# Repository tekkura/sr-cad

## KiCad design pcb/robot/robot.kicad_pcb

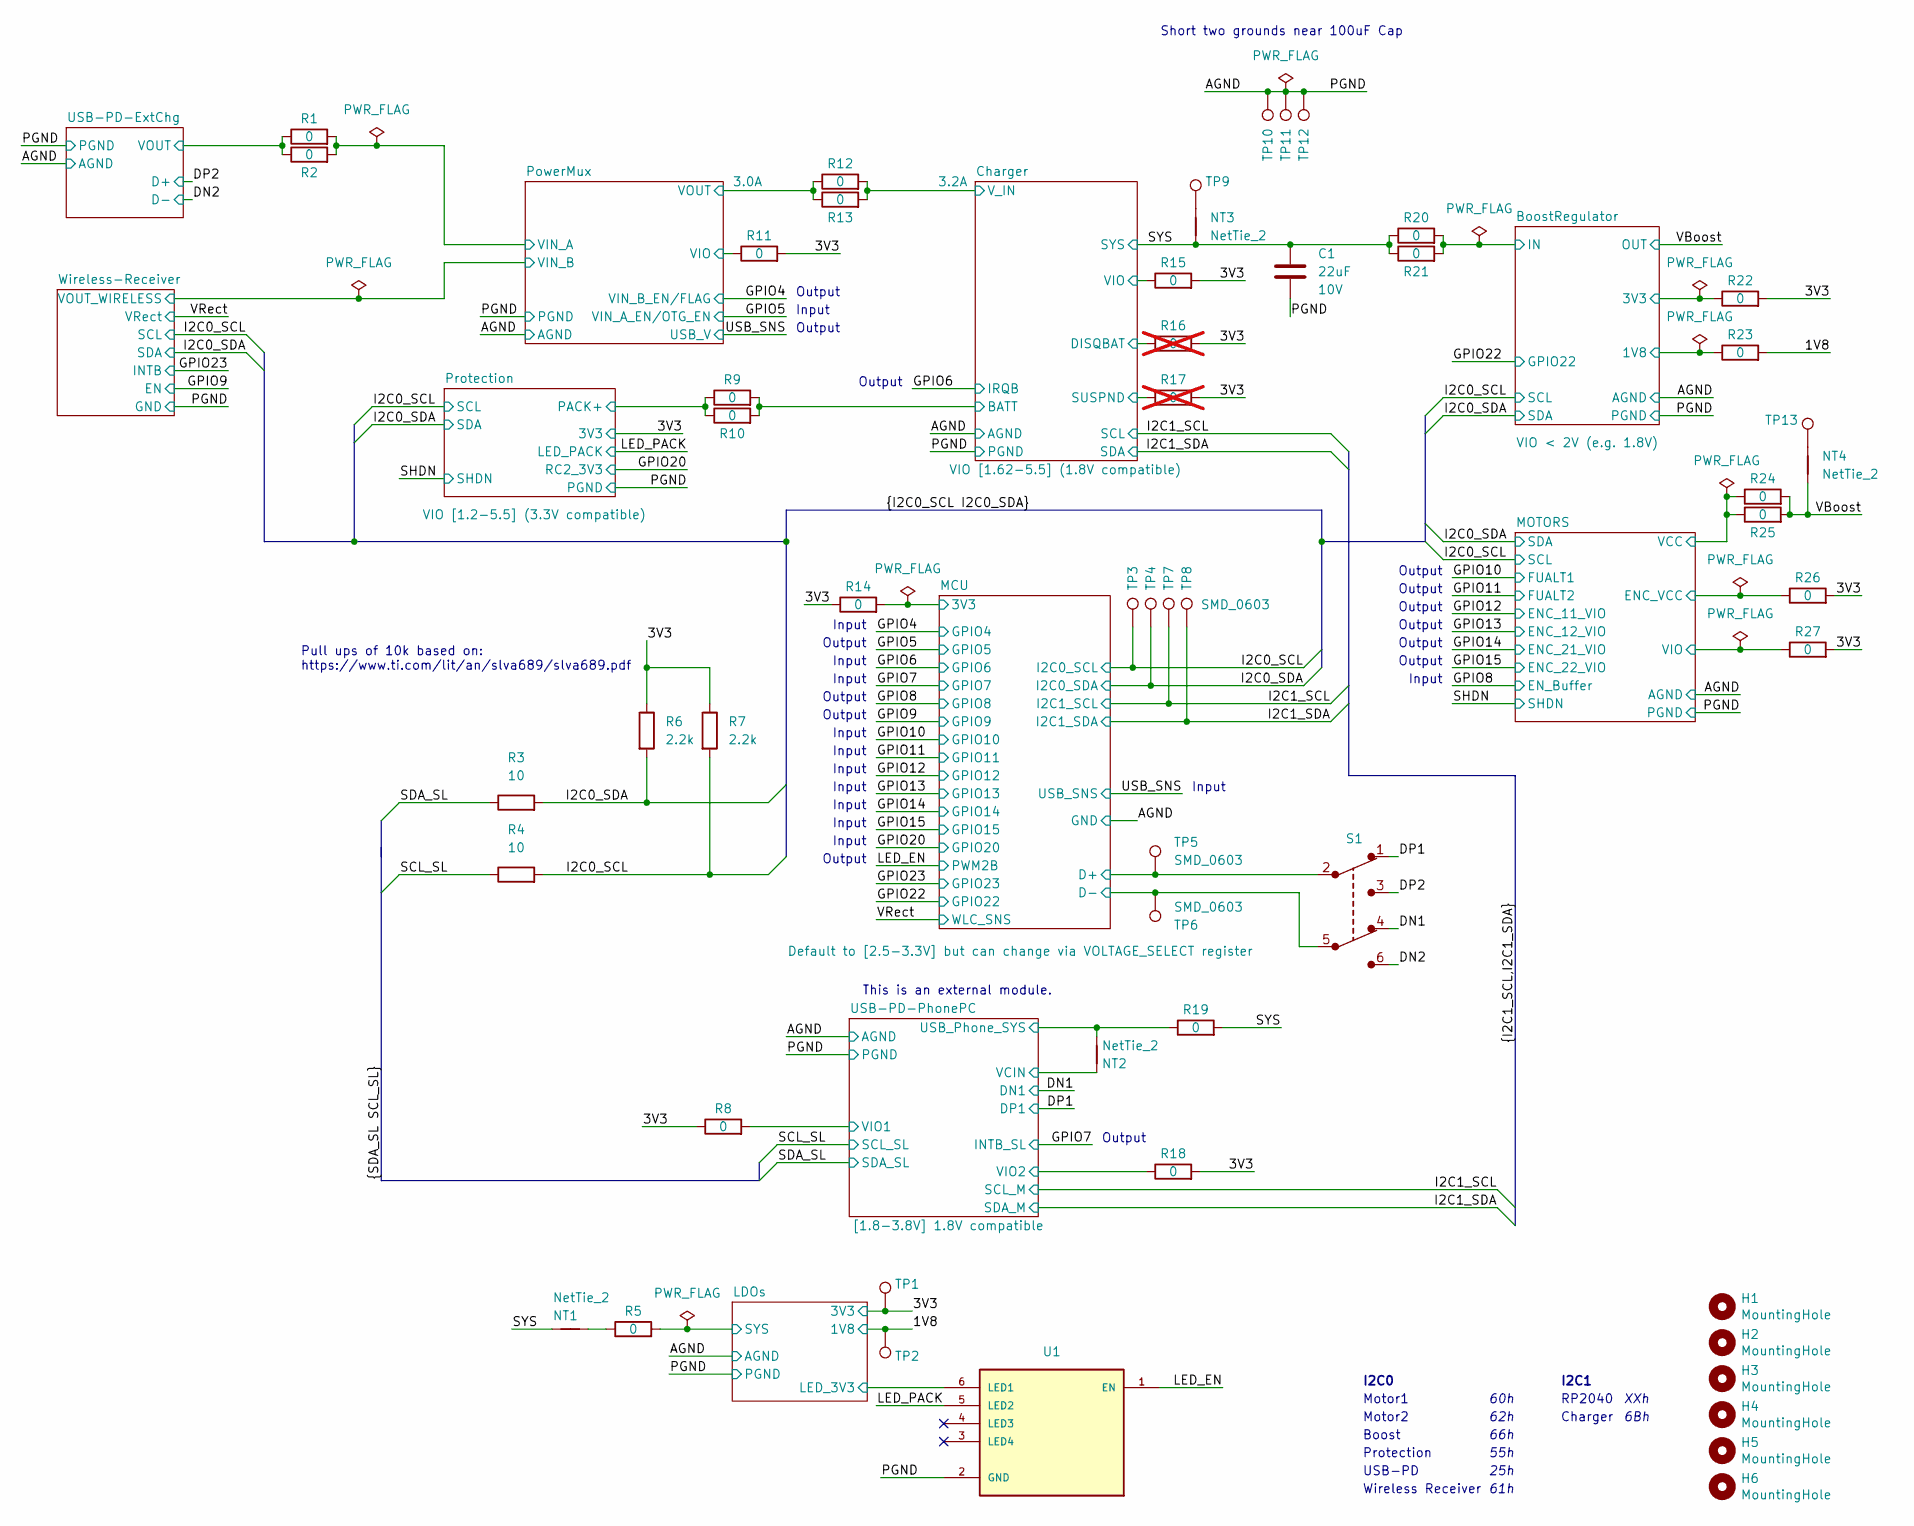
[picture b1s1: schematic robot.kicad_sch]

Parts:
C1: 22uF; C_0603_1608Metric; Part Number GRM188R61A226ME15D
H1, H2, H5, H6: MountingHole; MountingHole_2.2mm_M2_2mm_clearance; Part Number N/A
H3, H4: MountingHole; MountingHole_2.2mm_M2; Part Number N/A
NT1, NT2, NT3, NT4: NetTie_2; NetTie-_SMD_Pad6mil; Part Number N/A
R1, R2, R9, R10, R12, R13, R19, R20, R21, R24, R25: 0; R_0805_2012Metric; Part Number RMCF0805ZT0R00
R3, R4: 10; R_0402_1005Metric; Part Number RC0402FR-1310RL
R5, R8, R11, R14, R15, R18, R22, R23, R26, R27: 0; R_0603_1608Metric; Part Number RMCF0603ZT0R00
R6, R7: 2.2k; R_0603_1608Metric; Part Number RMCF0603JT2K20
R16, R17: 0; R_0603_1608Metric; Part Number RMCF0603ZT0R00; not fitted
S1: JS202011JCQN; SW_JS202011JCQN; Part Number JS202011JCQN
TP1, TP2, TP9, TP10, TP11, TP12, TP13: TestPoint; KEYSTONE_5002; Part Number 5002
TP3, TP4, TP5, TP6, TP7, TP8: SMD_0603; TestPoint_SMD_0603; Part Number RCUCTE
U1: AP2502KTR-G1; SOT95P280X145-6N; Part Number AP2502KTR-G1

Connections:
/1V8: R23.2, TP2.1; also elsewhere on the board
/3V3: R6.1, R7.1, R8.1, R11.2, R14.1, R15.2, R16.2, R17.2, R18.2, R22.2, R26.2, R27.2, TP1.1; also elsewhere on the board
/BoostRegulator/1V8: R23.1; also elsewhere on the board
/BoostRegulator/3V3: R22.1; also elsewhere on the board
/BoostRegulator/IN: R20.2, R21.2; also elsewhere on the board
/Charger/BATT: R9.2, R10.2; also elsewhere on the board
/Charger/DISQBAT: R16.1; also elsewhere on the board
/Charger/SUSPND: R17.1; also elsewhere on the board
/Charger/VIO: R15.1; also elsewhere on the board
/Charger/V_IN: R12.2, R13.2; also elsewhere on the board
/DN1: S1.4; also elsewhere on the board
/DN2: S1.6; also elsewhere on the board
/DP1: S1.1; also elsewhere on the board
/DP2: S1.3; also elsewhere on the board
/I2C0_SCL: R4.2, R7.2, TP3.1; also elsewhere on the board
/I2C0_SDA: R3.2, R6.2, TP4.1; also elsewhere on the board
/I2C1_SCL: TP7.1; also elsewhere on the board
/I2C1_SDA: TP8.1; also elsewhere on the board
/LDOs/LED_3V3: U1.6 (LED1); also elsewhere on the board
/LDOs/SYS: R5.2; also elsewhere on the board
/LED_EN: U1.1 (EN); also elsewhere on the board
/LED_PACK: U1.5 (LED2); also elsewhere on the board
/MCU/3V3: R14.2; also elsewhere on the board
/MCU/D+: S1.2, TP5.1; also elsewhere on the board
/MCU/D-: S1.5, TP6.1; also elsewhere on the board
/MOTORS/ENC_VCC: R26.1; also elsewhere on the board
/MOTORS/VCC: R24.1, R25.1; also elsewhere on the board
/MOTORS/VIO: R27.1; also elsewhere on the board
/PowerMux/VIN_A: R1.2, R2.2; also elsewhere on the board
/PowerMux/VIO: R11.1; also elsewhere on the board
/PowerMux/VOUT: R12.1, R13.1; also elsewhere on the board
/Protection/PACK+: R9.1, R10.1; also elsewhere on the board
/SCL_SL: R4.1; also elsewhere on the board
/SDA_SL: R3.1; also elsewhere on the board
/SYS: C1.1, NT1.1, NT3.2, R19.2, R20.1, R21.1; also elsewhere on the board
/USB-PD-ExtChg/VOUT: R1.1, R2.1; also elsewhere on the board
/USB-PD-PhonePC/USB_Phone_SYS: NT2.2, R19.1; also elsewhere on the board
/USB-PD-PhonePC/VCIN: NT2.1; also elsewhere on the board
/USB-PD-PhonePC/VIO1: R8.2; also elsewhere on the board
/USB-PD-PhonePC/VIO2: R18.1; also elsewhere on the board
/VBoost: NT4.2, R24.2, R25.2; also elsewhere on the board
GND: C1.2, TP10.1, TP11.1, TP12.1, U1.2 (GND); also elsewhere on the board
unnamed: NT1.2, R5.1
unnamed: NT3.1, TP9.1
unnamed: NT4.1, TP13.1

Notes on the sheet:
55h
Input
66h
Output
Protection
XXh
61h
Boost
I2C1
Wireless Receiver
Motor1
62h
Motor2
25h
Charger
This is an external module.
Pull ups of 10k based on: https://www.ti.com/lit/an/slva689/slva689.pdf
I2C0
USB-PD
RP2040
60h
6Bh
Short two grounds near 100uF Cap

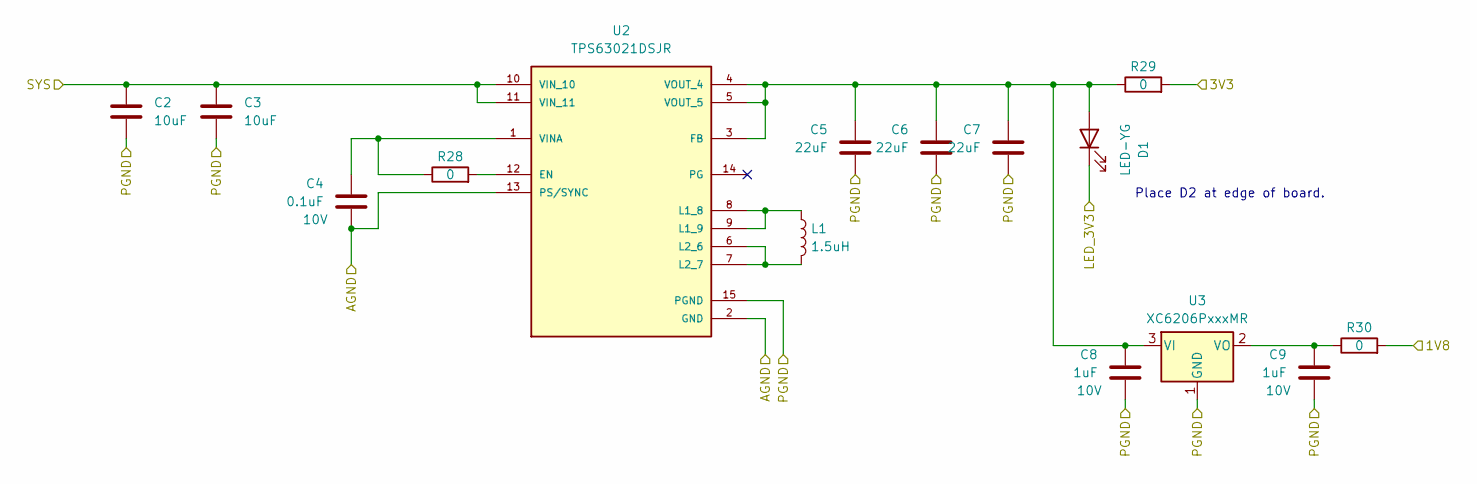
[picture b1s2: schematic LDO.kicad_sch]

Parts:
C2, C3: 10uF; C_0603_1608Metric; Part Number GRM188R61E106KA73J
C4: 0.1uF; C_0402_1005Metric; Part Number CL05A104KA5NNNC
C5, C6, C7: 22uF; C_0603_1608Metric; Part Number GRM188R61A226ME15D
C8, C9: 1uF; C_0402_1005Metric; Part Number GRM155R61E105KA12D
D1: LED-YG; B12H1UYG-20D000134U1930; Part Number B12H1UYG-20D000134U1930
L1: 1.5uH; NRS6028T1R5NMGJ; Part Number NRS6028T1R5NMGJ
R28, R29, R30: 0; R_0603_1608Metric; Part Number RMCF0603ZT0R00
U2: TPS63021DSJR; IC_TPS63021DSJR; PARTREV I; DigiKey_Part_Number 296-27259-1-ND
U3: XC6206PxxxMR; SOT-23-3; Part Number C49195704

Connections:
/1V8: R30.2; also elsewhere on the board
/3V3: R29.2; also elsewhere on the board
/LDOs/LED_3V3: D1.1 (K); also elsewhere on the board
/LDOs/SYS: C2.2, C3.2, U2.10 (VIN_10), U2.11 (VIN_11); also elsewhere on the board
GND: C2.1, C3.1, C4.2, C5.2, C6.2, C7.2, C8.2, C9.2, U2.2 (GND), U2.13 (PS/SYNC), U2.15 (PGND), U3.1 (GND); also elsewhere on the board
unnamed: C5.1, C6.1, C7.1, C8.1, D1.2 (A), R29.1, U2.3 (FB), U2.4 (VOUT_4), U2.5 (VOUT_5), U3.3 (VI)
unnamed: R28.2, U2.12 (EN)
unnamed: L1.1, U2.8 (L1_8), U2.9 (L1_9)
unnamed: L1.2, U2.6 (L2_6), U2.7 (L2_7)
unnamed: C4.1, R28.1, U2.1 (VINA)
unnamed: C9.1, R30.1, U3.2 (VO)

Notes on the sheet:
Place D2 at edge of board.

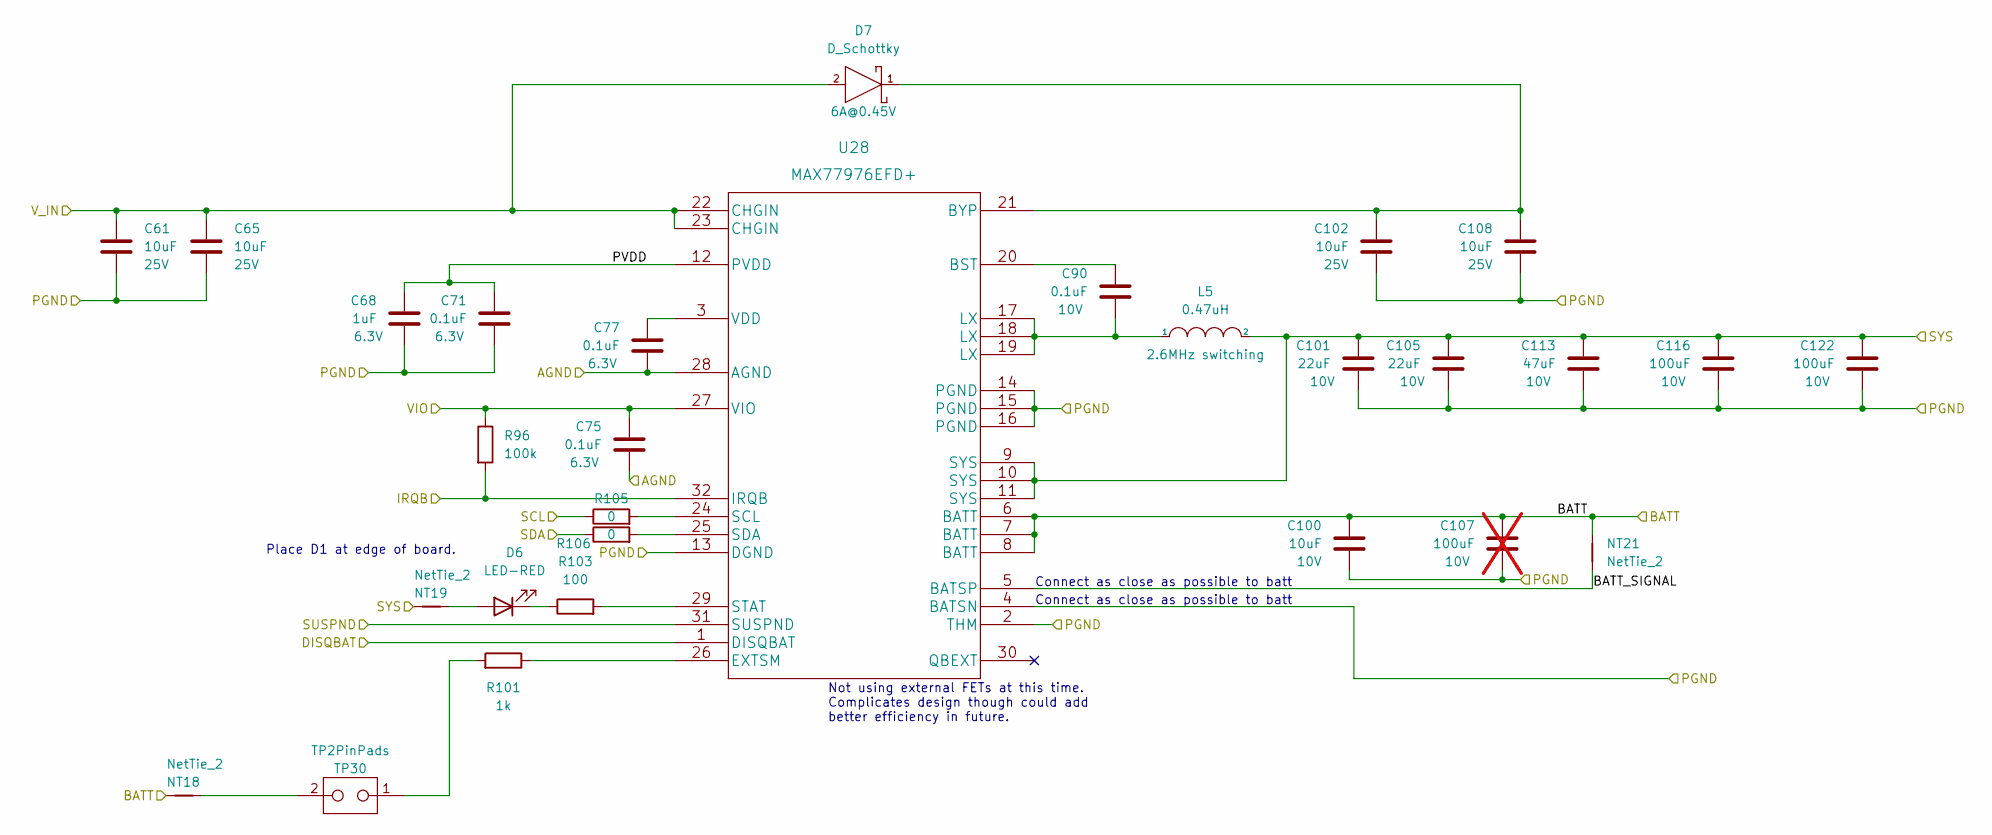
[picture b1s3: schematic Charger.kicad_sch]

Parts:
C61, C65, C100, C102, C108: 10uF; C_0603_1608Metric; Part Number GRM188R61E106KA73J
C68: 1uF; C_0402_1005Metric; Part Number GRM155R61E105KA12D
C71, C75, C77, C90: 0.1uF; C_0402_1005Metric; Part Number CL05A104KA5NNNC
C101, C105: 22uF; C_0603_1608Metric; Part Number GRM188R61A226ME15D
C107: 100uF; C_1206_3216Metric; Part Number GRM31CD80J107MEA8K; not fitted
C113: 47uF; C_0805_2012Metric; Part Number CL21A476MRYNNNE
C116, C122: 100uF; C_1206_3216Metric; Part Number GRM31CD80J107MEA8K
D6: LED-RED; B12H1UYG-20D000134U1930; Part Number B12H1USD-20D000234U1930
D7: D_Schottky; SD2114S040S8R0; Part Number SD2114S040S8R0
L5: 0.47uH; Vishay-IHLP-2020BZ-FP_1.905x2.79-3D_2.0-0-0-MFG; Part Number IHLP2020BZERR47M01
NT18, NT19, NT21: NetTie_2; NetTie-_SMD_Pad6mil; Part Number N/A
R96: 100k; R_0603_1608Metric; Part Number WR06X1003FTL
R101: 1k; R_0402_1005Metric; Part Number WR04X102 JTL
R103: 100; R_0603_1608Metric; Part Number RMCF0603JT100R
R105, R106: 0; R_0603_1608Metric; Part Number RMCF0603ZT0R00
TP30: TP2PinPads; TestPoint_2Pads_Pitch2mm_SMD; Part Number N/A
U28: MAX77976EFD+; MAX77976; Part Number MAX77976EFD+

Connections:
/Charger/BATT: C100.1, C107.1, NT18.1, NT21.1, U28.6 (BATT), U28.7 (BATT), U28.8 (BATT); also elsewhere on the board
/Charger/BATT_SIGNAL: NT21.2, U28.5 (BATSP)
/Charger/DISQBAT: U28.1 (DISQBAT); also elsewhere on the board
/Charger/PVDD: C68.1, C71.1, U28.12 (PVDD)
/Charger/SUSPND: U28.31 (SUSPND); also elsewhere on the board
/Charger/VIO: C75.1, R96.1, U28.27 (VIO); also elsewhere on the board
/Charger/V_IN: C61.1, C65.1, D7.2 (Anode), U28.22 (CHGIN), U28.23 (CHGIN); also elsewhere on the board
/GPIO6: R96.2, U28.32 (IRQB); also elsewhere on the board
/I2C1_SCL: R105.1; also elsewhere on the board
/I2C1_SDA: R106.1; also elsewhere on the board
/SYS: C101.1, C105.1, C113.1, C116.1, C122.1, L5.2, NT19.1, U28.9 (SYS), U28.10 (SYS), U28.11 (SYS); also elsewhere on the board
GND: C61.2, C65.2, C68.2, C71.2, C75.2, C77.2, C100.2, C101.2, C102.2, C105.2, C107.2, C108.2, C113.2, C116.2, C122.2, U28.2 (THM), U28.4 (BATSN), U28.13 (DGND), U28.14 (PGND), U28.15 (PGND), U28.16 (PGND), U28.28 (AGND); also elsewhere on the board
unnamed: C90.2, L5.1, U28.17 (LX), U28.18 (LX), U28.19 (LX)
unnamed: D6.2 (A), NT19.2
unnamed: D6.1 (K), R103.1
unnamed: C102.1, C108.1, D7.1 (Cathode), U28.21 (BYP)
unnamed: NT18.2, TP30.2
unnamed: R101.2, TP30.1
unnamed: C90.1, U28.20 (BST)
unnamed: R101.1, U28.26 (EXTSM)
unnamed: R105.2, U28.24 (SCL)
unnamed: R106.2, U28.25 (SDA)
unnamed: R103.2, U28.29 (STAT)
unnamed: C77.1, U28.3 (VDD)

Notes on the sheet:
Not using external FETs at this time. Complicates design though could add better efficiency in future.
Connect as close as possible to batt
Place D1 at edge of board.

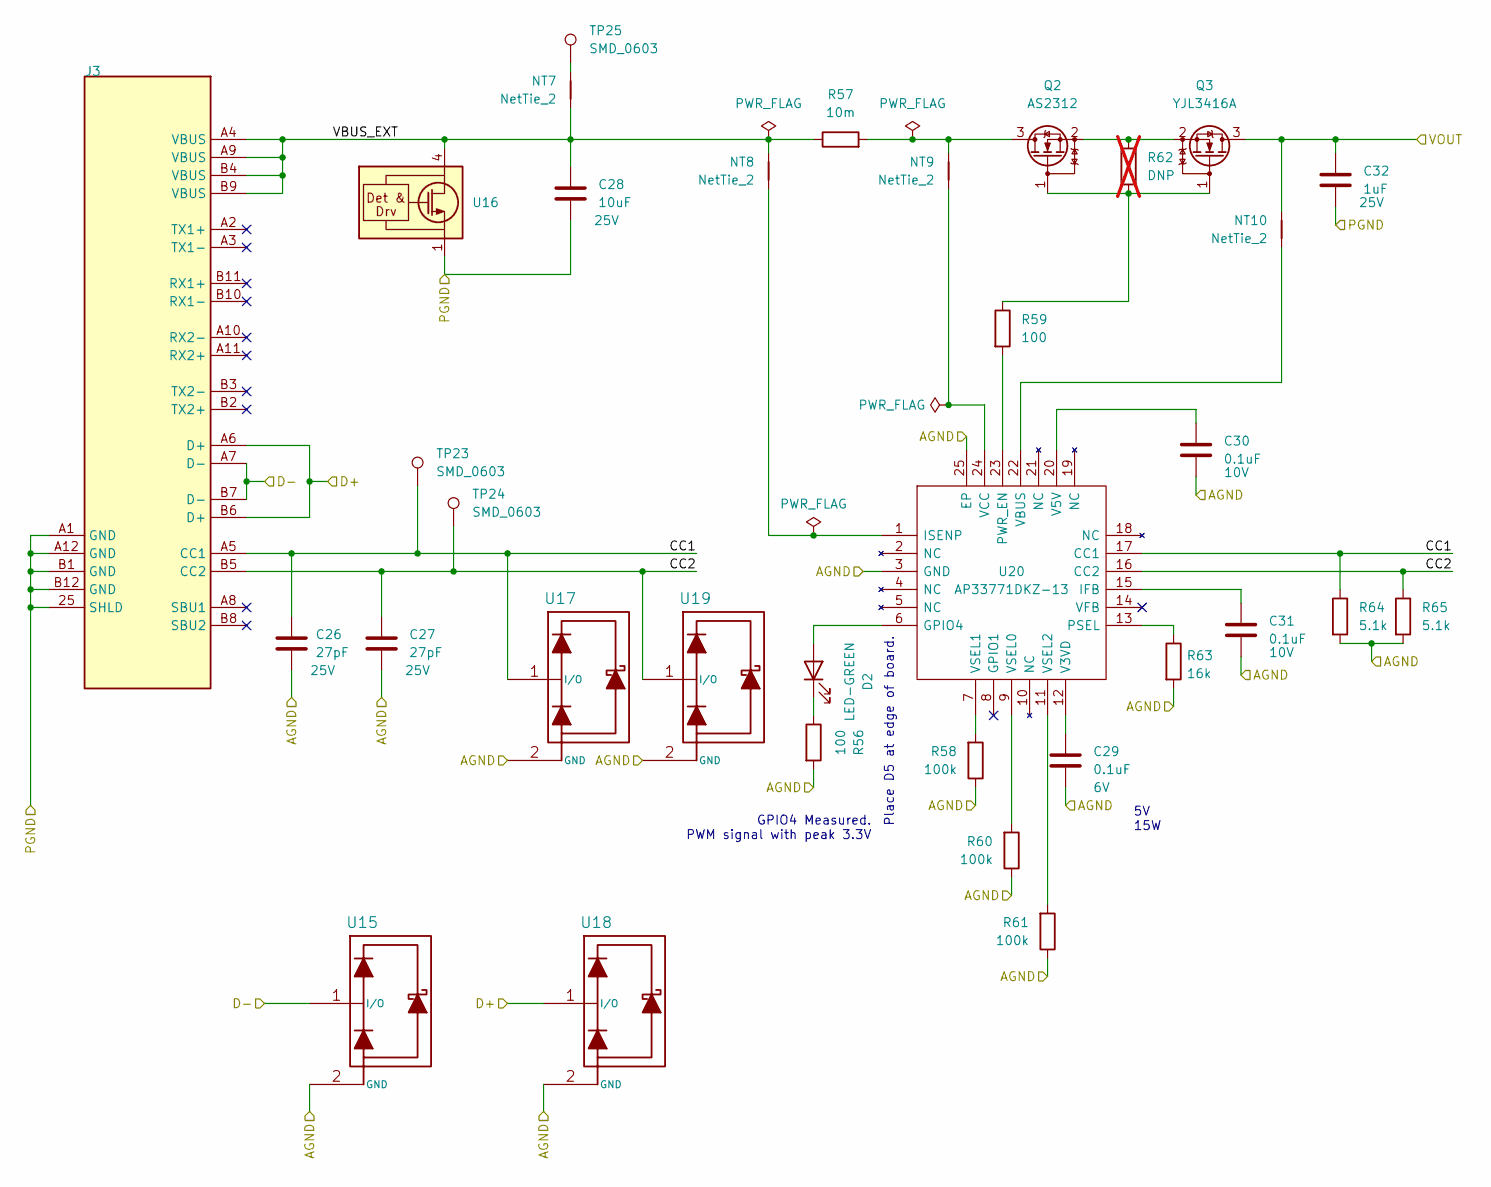
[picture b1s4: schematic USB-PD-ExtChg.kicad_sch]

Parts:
C26, C27: 27pF; C_0402_1005Metric; Part Number GRM1555C1H270JA01J
C28: 10uF; C_0603_1608Metric; Part Number GRM188R61E106KA73J
C29, C30, C31: 0.1uF; C_0402_1005Metric; Part Number CL05A104KA5NNNC
C32: 1uF; C_0402_1005Metric; Part Number GRM155R61E105KA12D
D2: LED-GREEN; B12H1UYG-20D000134U1930; Part Number B12H1NG--20D000134U1930
J3: USBC_Receptacle_SMD_RA; CON_USB3.1-C_RCPT_SMD_RA_ACP_12401610E4#2A; Part Number 12401610E4#2A
NT7, NT8, NT9, NT10: NetTie_2; NetTie-_SMD_Pad6mil; Part Number N/A
Q2: AS2312; SOT-23; Part Number AS2312
Q3: YJL3416A; SOT-23; Part Number YJL3416A
R56, R59: 100; R_0603_1608Metric; Part Number RMCF0603JT100R
R57: 10m; R_1206_3216Metric; Part Number ERJ-8CWJR010V
R58, R60, R61: 100k; R_0603_1608Metric; Part Number WR06X1003FTL
R62: DNP; R_0603_1608Metric; Part Number DNP; not fitted
R63: 16k; R_0603_1608Metric; Part Number RMCF0603FT16K0
R64, R65: 5.1k; R_0603_1608Metric; Part Number RMCF0603JT5K10
TP23, TP24, TP25: SMD_0603; TestPoint_SMD_0603; Part Number RCUCTE
U15, U17, U18, U19: TPD1E05U06; TPD1E05U06DPYR; Part Number TPD1E05U06DPYR
U16: TVS0500DRV; TVS0500DRVR; Part Number TVS0500DRVR
U20: AP33771DKZ-13; AP33771DKZ13; Part Number AP33771DKZ-13

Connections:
/DN2: J3.A7 (D-), J3.B7 (D-), U15.1 (I/O); also elsewhere on the board
/DP2: J3.A6 (D+), J3.B6 (D+), U18.1 (I/O); also elsewhere on the board
/USB-PD-ExtChg/CC1: C26.1, J3.A5 (CC1), R64.1, TP23.1, U17.1 (I/O), U20.17 (CC1)
/USB-PD-ExtChg/CC2: C27.1, J3.B5 (CC2), R65.1, TP24.1, U19.1 (I/O), U20.16 (CC2)
/USB-PD-ExtChg/VBUS_EXT: C28.1, J3.A4 (VBUS), J3.A9 (VBUS), J3.B4 (VBUS), J3.B9 (VBUS), NT7.2, NT8.1, R57.1, U16.4 (IN), U16.5 (IN), U16.6 (IN)
/USB-PD-ExtChg/VOUT: C32.1, NT10.1, Q3.3 (D); also elsewhere on the board
GND: C26.2, C27.2, C28.2, C29.2, C30.2, C31.2, C32.2, J3.25 (SHLD), J3.A1 (GND), J3.A12 (GND), J3.B1 (GND), J3.B12 (GND), R56.2, R58.1, R60.1, R61.1, R63.2, R64.2, R65.2, U15.2 (GND), U16.1 (GND), U16.2 (GND), U16.3 (GND), U16.7 (GND), U17.2 (GND), U18.2 (GND), U19.2 (GND), U20.3 (GND), U20.25 (EP); also elsewhere on the board
unnamed: D2.2 (A), U20.6 (GPIO4)
unnamed: D2.1 (K), R56.1
unnamed: NT7.1, TP25.1
unnamed: NT9.1, Q2.3 (D), R57.2
unnamed: Q2.1 (G), Q3.1 (G), R59.1, R62.2
unnamed: Q2.2 (S), Q3.2 (S), R62.1
unnamed: C31.1, U20.15 (IFB)
unnamed: NT8.2, U20.1 (ISENP)
unnamed: R63.1, U20.13 (PSEL)
unnamed: R59.2, U20.23 (PWR_EN)
unnamed: C29.1, U20.12 (V3VD)
unnamed: C30.1, U20.20 (V5V)
unnamed: NT10.2, U20.22 (VBUS)
unnamed: NT9.2, U20.24 (VCC)
unnamed: R60.2, U20.9 (VSEL0)
unnamed: R58.2, U20.7 (VSEL1)
unnamed: R61.2, U20.11 (VSEL2)

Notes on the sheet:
5V 15W
Place D5 at edge of board.
GPIO4 Measured. PWM signal with peak 3.3V

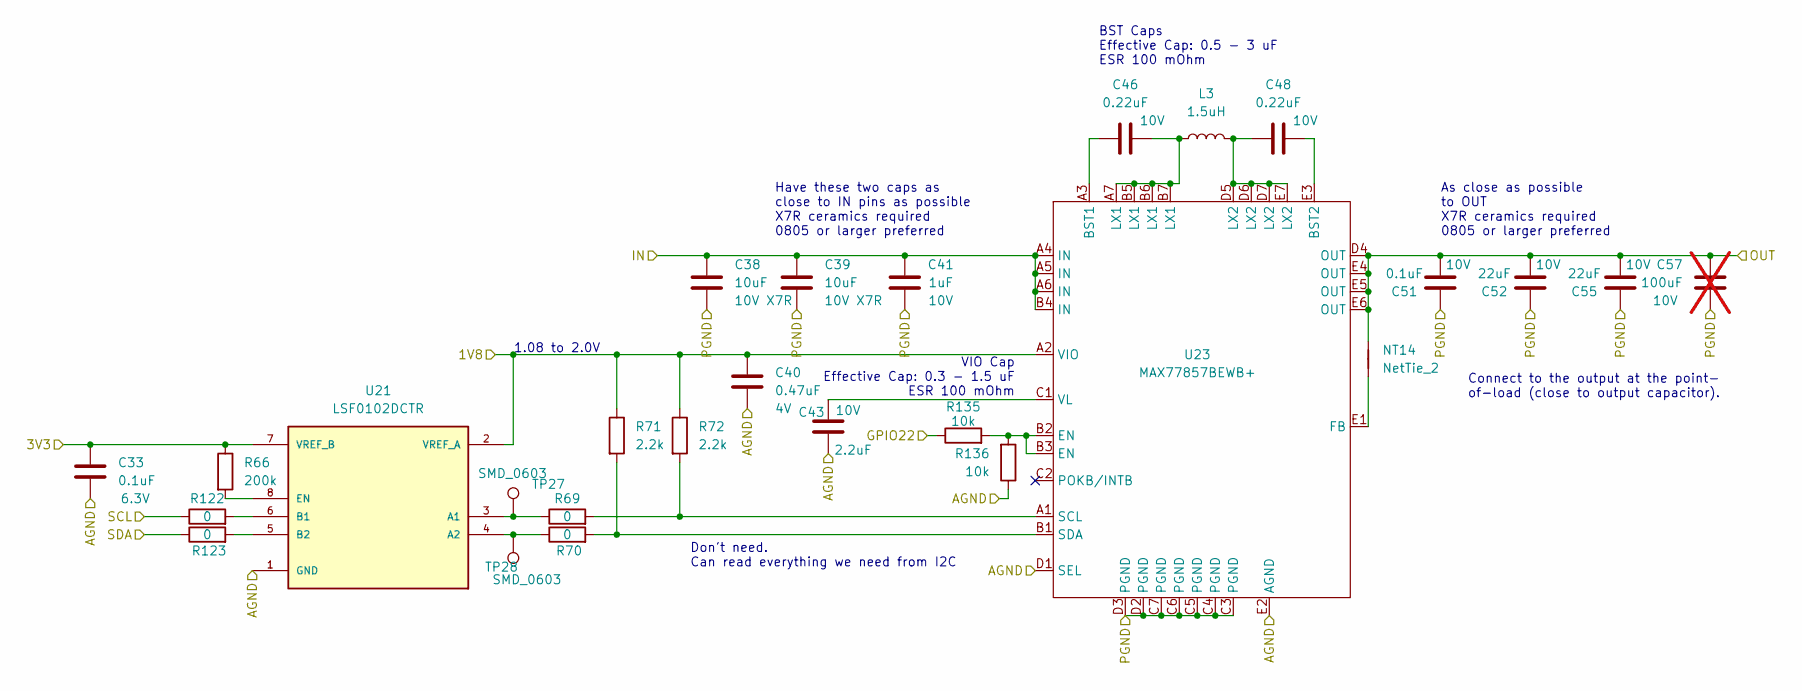
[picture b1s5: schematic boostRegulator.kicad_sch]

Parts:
C33, C51: 0.1uF; C_0402_1005Metric; Part Number CL05A104KA5NNNC
C38, C39: 10uF; C_0603_1608Metric; Part Number GRM188R61E106KA73J
C40: 0.47uF; C_0603_1608Metric; Part Number CL10B474KO8NNNC
C41: 1uF; C_0402_1005Metric; Part Number GRM155R61E105KA12D
C43: 2.2uF; C_0603_1608Metric; Part Number CL10A225KP8NNNC
C46, C48: 0.22uF; C_0603_1608Metric; Part Number CL10B224KA8NNNC
C52, C55: 22uF; C_0603_1608Metric; Part Number GRM188R61A226ME15D
C57: 100uF; C_1206_3216Metric; Part Number GRM31CD80J107MEA8K; not fitted
L3: 1.5uH; NRS6028T1R5NMGJ; Part Number NRS6028T1R5NMGJ
NT14: NetTie_2; NetTie-_SMD_Pad6mil; Part Number N/A
R66: 200k; R_0603_1608Metric; Part Number RMCF0603JT200K
R69, R70, R122, R123: 0; R_0603_1608Metric; Part Number RMCF0603ZT0R00
R71, R72: 2.2k; R_0603_1608Metric; Part Number RMCF0603JT2K20
R135, R136: 10k; R_0603_1608Metric; Part Number WR06X1002FTL
TP27, TP28: SMD_0603; TestPoint_SMD_0603; Part Number RCUCTE
U21: LSF0102DCTR; SOP65P400X130-8N; Part Number LSF0102DCTR
U23: MAX77857BEWB+; WLP-35_7x5_2.828x2.028mm; Part Number MAX77857BEWB+

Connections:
/BoostRegulator/1V8: C40.1, R71.1, R72.1, U21.2 (VREF_A), U23.A2 (VIO); also elsewhere on the board
/BoostRegulator/3V3: C33.1, R66.1, U21.7 (VREF_B); also elsewhere on the board
/BoostRegulator/IN: C38.1, C39.1, C41.2, U23.A4 (IN), U23.A5 (IN), U23.A6 (IN), U23.B4 (IN); also elsewhere on the board
/GPIO22: R135.1; also elsewhere on the board
/I2C0_SCL: R122.1; also elsewhere on the board
/I2C0_SDA: R123.1; also elsewhere on the board
/VBoost: C51.2, C52.2, C55.2, C57.1, NT14.1, U23.D4 (OUT), U23.E4 (OUT), U23.E5 (OUT), U23.E6 (OUT); also elsewhere on the board
GND: C33.2, C38.2, C39.2, C40.2, C41.1, C43.2, C51.1, C52.1, C55.1, C57.2, R136.1, U21.1 (GND), U23.C3 (PGND), U23.C4 (PGND), U23.C5 (PGND), U23.C6 (PGND), U23.C7 (PGND), U23.D1 (SEL), U23.D2 (PGND), U23.D3 (PGND), U23.E2 (AGND); also elsewhere on the board
unnamed: C46.2, L3.1, U23.A7 (LX1), U23.B5 (LX1), U23.B6 (LX1), U23.B7 (LX1)
unnamed: C48.1, L3.2, U23.D5 (LX2), U23.D6 (LX2), U23.D7 (LX2), U23.E7 (LX2)
unnamed: R135.2, R136.2, U23.B2 (EN), U23.B3 (EN)
unnamed: R69.1, TP27.1, U21.3 (A1)
unnamed: R70.1, TP28.1, U21.4 (A2)
unnamed: R122.2, U21.6 (B1)
unnamed: R123.2, U21.5 (B2)
unnamed: R66.2, U21.8 (EN)
unnamed: C46.1, U23.A3 (BST1)
unnamed: C48.2, U23.E3 (BST2)
unnamed: NT14.2, U23.E1 (FB)
unnamed: R69.2, R72.2, U23.A1 (SCL)
unnamed: R70.2, R71.2, U23.B1 (SDA)
unnamed: C43.1, U23.C1 (VL)

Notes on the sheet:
Have these two caps as close to IN pins as possible X7R ceramics required 0805 or larger preferred
Connect to the output at the point- of-load (close to output capacitor).
Don't need. Can read everything we need from I2C
BST Caps Effective Cap: 0.5 - 3 uF ESR 100 mOhm
1.08 to 2.0V
As close as possible to OUT X7R ceramics required 0805 or larger preferred
VIO Cap Effective Cap: 0.3 - 1.5 uF ESR 100 mOhm

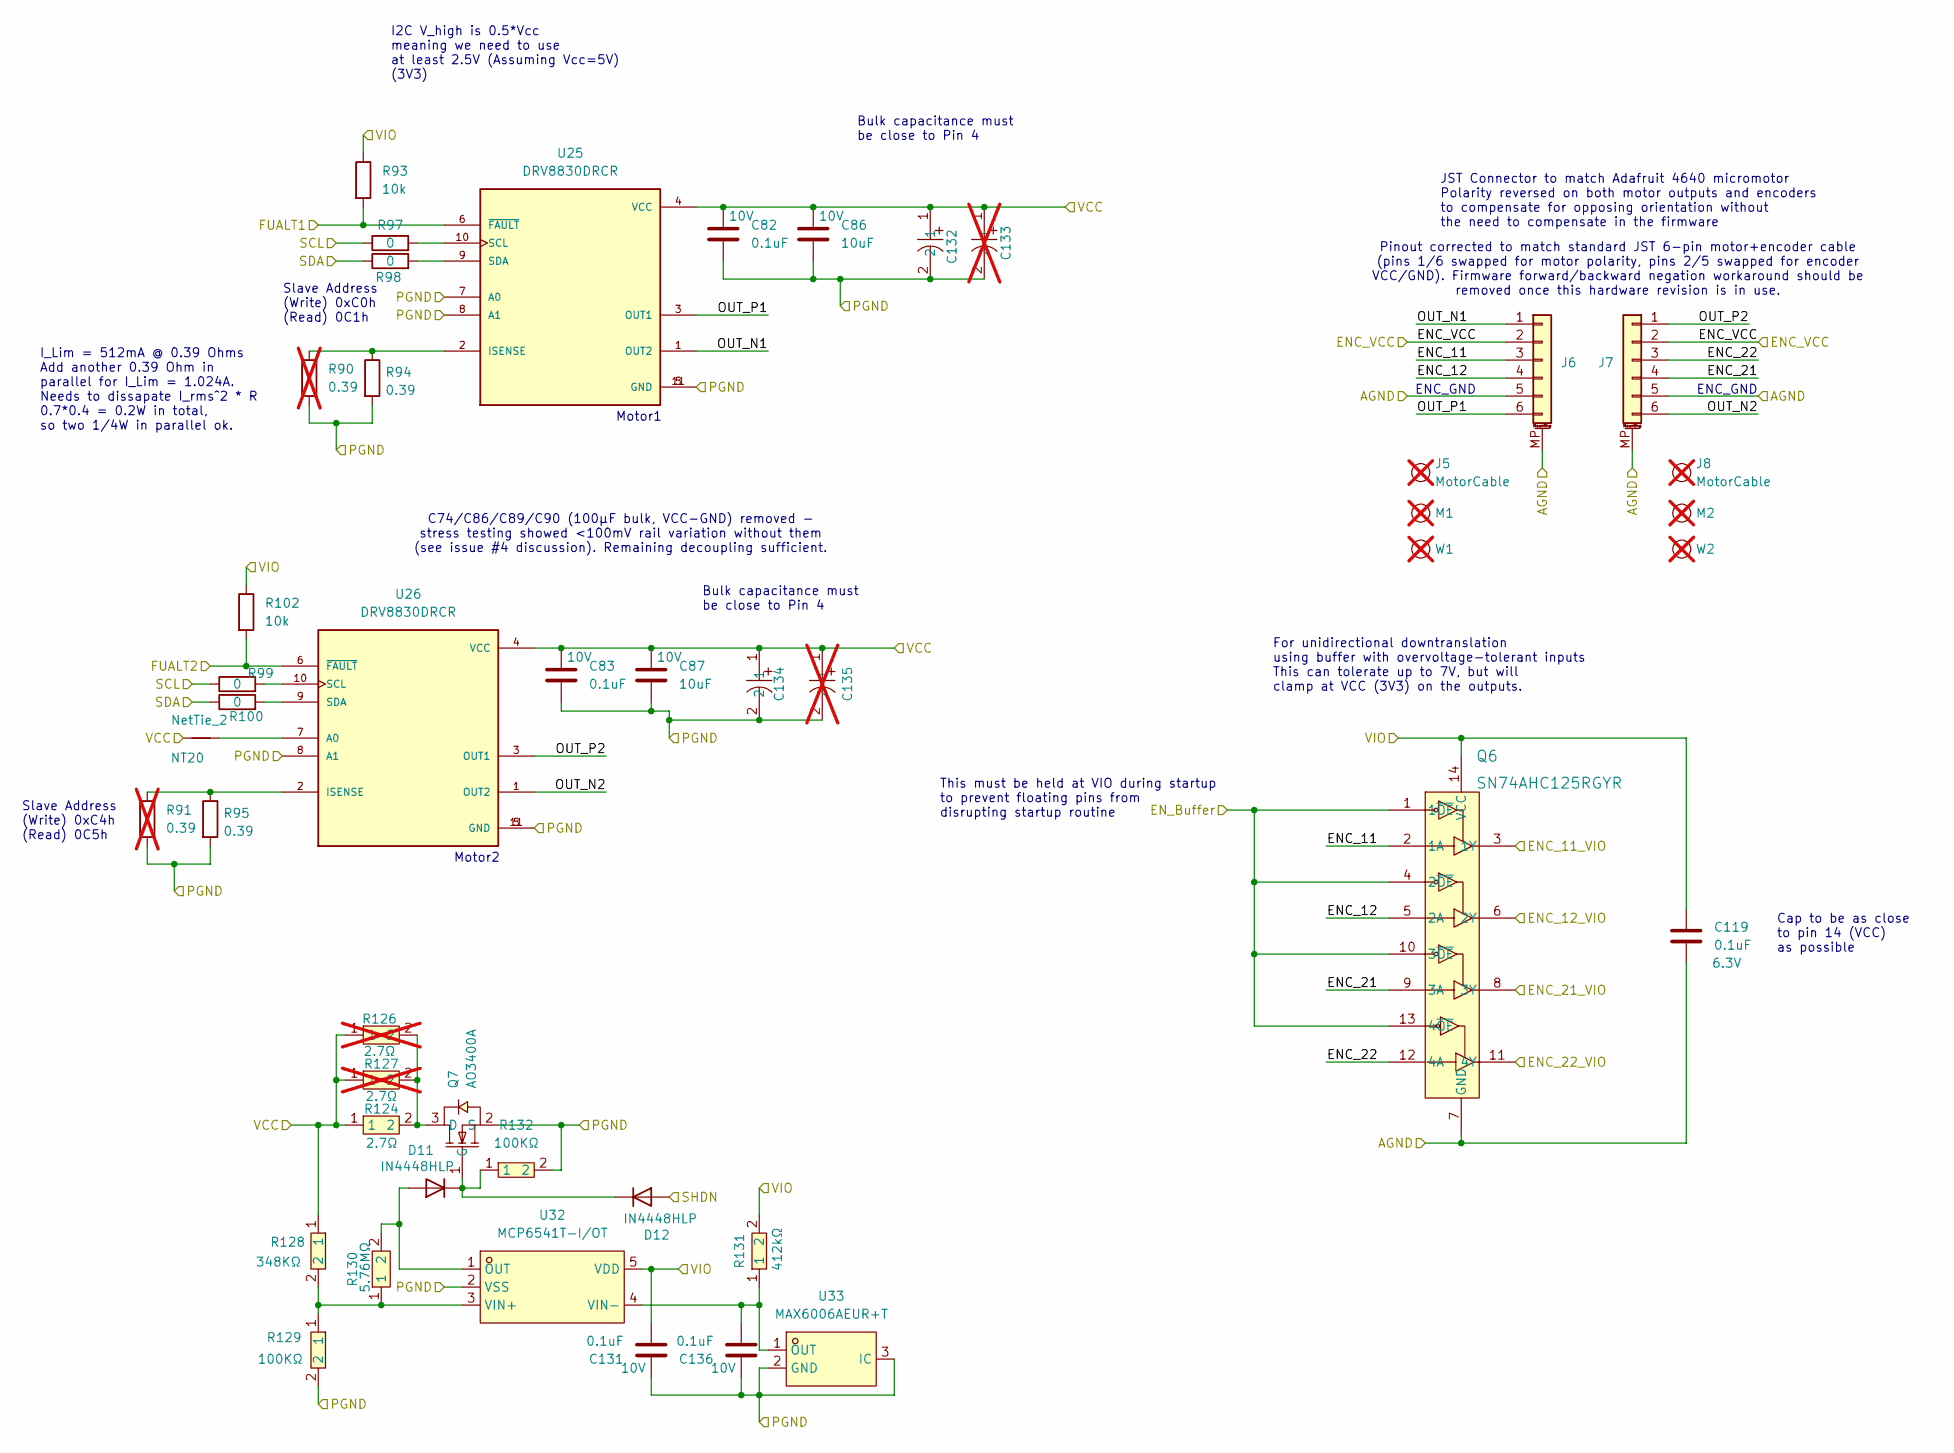
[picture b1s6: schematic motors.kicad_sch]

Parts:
C82, C83, C119, C131, C136: 0.1uF; C_0402_1005Metric; Part Number CL05A104KA5NNNC
C86, C87: 10uF; C_0603_1608Metric; Part Number GRM188R61E106KA73J
C132: APXK160ARA101MF611; CAP-SMD_BD6.3-L6.6-W6.6-FD; MPN APXK160ARA101MF611; LCSC Part C2162384
C133: APXK160ARA101MF611; CAP-SMD_BD6.3-L6.6-W6.6-FD; MPN APXK160ARA101MF611; LCSC Part C2162384; not fitted
C134: APXK160ARA101MF611; CAP-SMD_BD6.3-L6.6-W6.6-FD; Part Number APXK160ARA101MF611; LCSC Part C2162384
C135: APXK160ARA101MF611; CAP-SMD_BD6.3-L6.6-W6.6-FD; Part Number APXK160ARA101MF611; LCSC Part C2162384; not fitted
D11, D12: IN4448HLP; D_0402_1005Metric; Part Number 1N4448HLP-7
J5, J8: MotorCable; Part Number A06ZR06ZR28H51B; not fitted
J6, J7: Conn_01x06_MountingPin; CONN_B6B-ZR-SM4-TF_JST; Part Number B6B-ZR-SM4-TF
M1, M2: Part Number 4639; not fitted
NT20: NetTie_2; NetTie-_SMD_Pad6mil; Part Number N/A
Q6: SN74AHC125RGYR; Part Number SN74AHC125RGYR
Q7: AO3400A; SOT-23-3_L2.9-W1.3-P1.90-LS2.4-BR; Part Number AO3400A; LCSC Part C20917
R90, R91: 0.39; R_0603_1608Metric; Part Number ERJ-3RQJR39V; not fitted
R93, R102: 10k; R_0603_1608Metric; Part Number WR06X1002FTL
R94, R95: 0.39; R_0603_1608Metric; Part Number ERJ-3RQJR39V
R97, R98, R99, R100: 0; R_0603_1608Metric; Part Number RMCF0603ZT0R00
R124: 2.7Ω; R2512; Part Number FRC2512F2R70TS; LCSC Part C2999529
R126, R127: 2.7Ω; R2512; Part Number FRC2512F2R70TS; LCSC Part C2999529; not fitted
R128: 348KΩ; R0603; Part Number 0603WAF3483T5E; LCSC Part C23006
R129, R132: 100KΩ; R0603; Part Number 0603WAF1003T5E; LCSC Part C25803
R130: 5.76MΩ; R0603; Part Number 0603WAF5904T5E; LCSC Part C422915
R131: 412kΩ; R0402; Part Number 0402WGF4123TCE; LCSC Part C27008
U25, U26: DRV8830DRCR; IC_DRV8830DRCR; Part Number DRV8830DRCR
U32: MCP6541T-I/OT; SOT-23-5_L3.0-W1.7-P0.95-LS2.8-BR; Part Number MCP6541T-I/OT; LCSC Part C80839
U33: MAX6006AEUR+T; SOT-23-3_L2.9-W1.3-P0.95-LS2.4-BR; Part Number MAX6006AEUR+T; LCSC Part C2830546
W1, W2: Part Number 4939; not fitted

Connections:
/GPIO8: Q6.1 (1~OE), Q6.4 (2~OE), Q6.10 (3~OE), Q6.13 (4~OE); also elsewhere on the board
/GPIO10: R93.2, U25.6 (~FAULT); also elsewhere on the board
/GPIO11: R102.2, U26.6 (~FAULT); also elsewhere on the board
/GPIO12: Q6.3 (1Y); also elsewhere on the board
/GPIO13: Q6.6 (2Y); also elsewhere on the board
/GPIO14: Q6.8 (3Y); also elsewhere on the board
/GPIO15: Q6.11 (4Y); also elsewhere on the board
/I2C0_SCL: R97.1, R99.1; also elsewhere on the board
/I2C0_SDA: R98.1, R100.1; also elsewhere on the board
/MOTORS/ENC_11: J6.3, Q6.2 (1A)
/MOTORS/ENC_12: J6.4, Q6.5 (2A)
/MOTORS/ENC_21: J7.4, Q6.9 (3A)
/MOTORS/ENC_22: J7.3, Q6.12 (4A)
/MOTORS/ENC_VCC: J6.2, J7.2; also elsewhere on the board
/MOTORS/OUT_N1: J6.1, U25.1 (OUT2)
/MOTORS/OUT_N2: J7.6, U26.1 (OUT2)
/MOTORS/OUT_P1: J6.6, U25.3 (OUT1)
/MOTORS/OUT_P2: J7.1, U26.3 (OUT1)
/MOTORS/VCC: C82.1, C83.1, C86.1, C87.1, C132.1, C133.1, C134.1, C135.1, NT20.2, R124.1, R126.1, R127.1, R128.1, U25.4 (VCC), U26.4 (VCC); also elsewhere on the board
/MOTORS/VIO: C119.1, C131.2, Q6.14 (VCC), R93.1, R102.1, R131.2, U32.5 (VDD); also elsewhere on the board
/SHDN: D12.2 (A); also elsewhere on the board
GND: C82.2, C83.2, C86.2, C87.2, C119.2, C131.1, C132.2, C133.2, C134.2, C135.2, C136.1, J6.5, J6.MP (MountPin), J7.5, J7.MP (MountPin), Q6.7 (GND), Q6.PAD (GND), Q7.2 (S), R90.2, R91.2, R94.2, R95.2, R129.2, R132.2, U25.5 (GND), U25.7 (A0), U25.8 (A1), U25.11 (GND), U26.5 (GND), U26.8 (A1), U26.11 (GND), U32.2 (VSS), U33.2 (GND), U33.3 (IC); also elsewhere on the board
unnamed: D11.2 (A), R130.2, U32.1 (OUT)
unnamed: D11.1 (K), D12.1 (K), Q7.1 (G), R132.1
unnamed: Q7.3 (D), R124.2, R126.2, R127.2
unnamed: R90.1, R94.1, U25.2 (ISENSE)
unnamed: R97.2, U25.10 (SCL)
unnamed: R98.2, U25.9 (SDA)
unnamed: NT20.1, U26.7 (A0)
unnamed: R91.1, R95.1, U26.2 (ISENSE)
unnamed: R99.2, U26.10 (SCL)
unnamed: R100.2, U26.9 (SDA)
unnamed: R128.2, R129.1, R130.1, U32.3 (VIN+)
unnamed: C136.2, R131.1, U32.4 (VIN-), U33.1 (OUT)

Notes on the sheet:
Motor1
Bulk capacitance must be close to Pin 4
Motor2
Slave Address (Write) 0xC0h (Read) 0C1h
ENC_GND
For unidirectional downtranslation using buffer with overvoltage-tolerant inputs This can tolerate up to 7V, but will clamp at VCC (3V3) on the outputs.
This must be held at VIO during startup to prevent floating pins from disrupting startup routine
C74/C86/C89/C90 (100µF bulk, VCC-GND) removed - stress testing showed <100mV rail variation without them (see issue #4 discussion). Remaining decoupling sufficient.
I2C V_high is 0.5*Vcc meaning we need to use at least 2.5V (Assuming Vcc=5V) (3V3)
JST Connector to match Adafruit 4640 micromotor Polarity reversed on both motor outputs and encoders to compensate for opposing orientation without the need to compensate in the firmware
Cap to be as close to pin 14 (VCC) as possible
Pinout corrected to match standard JST 6-pin motor+encoder cable (pins 1/6 swapped for motor polarity, pins 2/5 swapped for encoder VCC/GND). Firmware forward/backward negation workaround should be removed once this hardware revision is in use.
I_Lim = 512mA @ 0.39 Ohms Add another 0.39 Ohm in parallel for I_Lim = 1.024A. Needs to dissapate I_rms^2 * R 0.7*0.4 = 0.2W in total, so two 1/4W in parallel ok.
Slave Address (Write) 0xC4h (Read) 0C5h
